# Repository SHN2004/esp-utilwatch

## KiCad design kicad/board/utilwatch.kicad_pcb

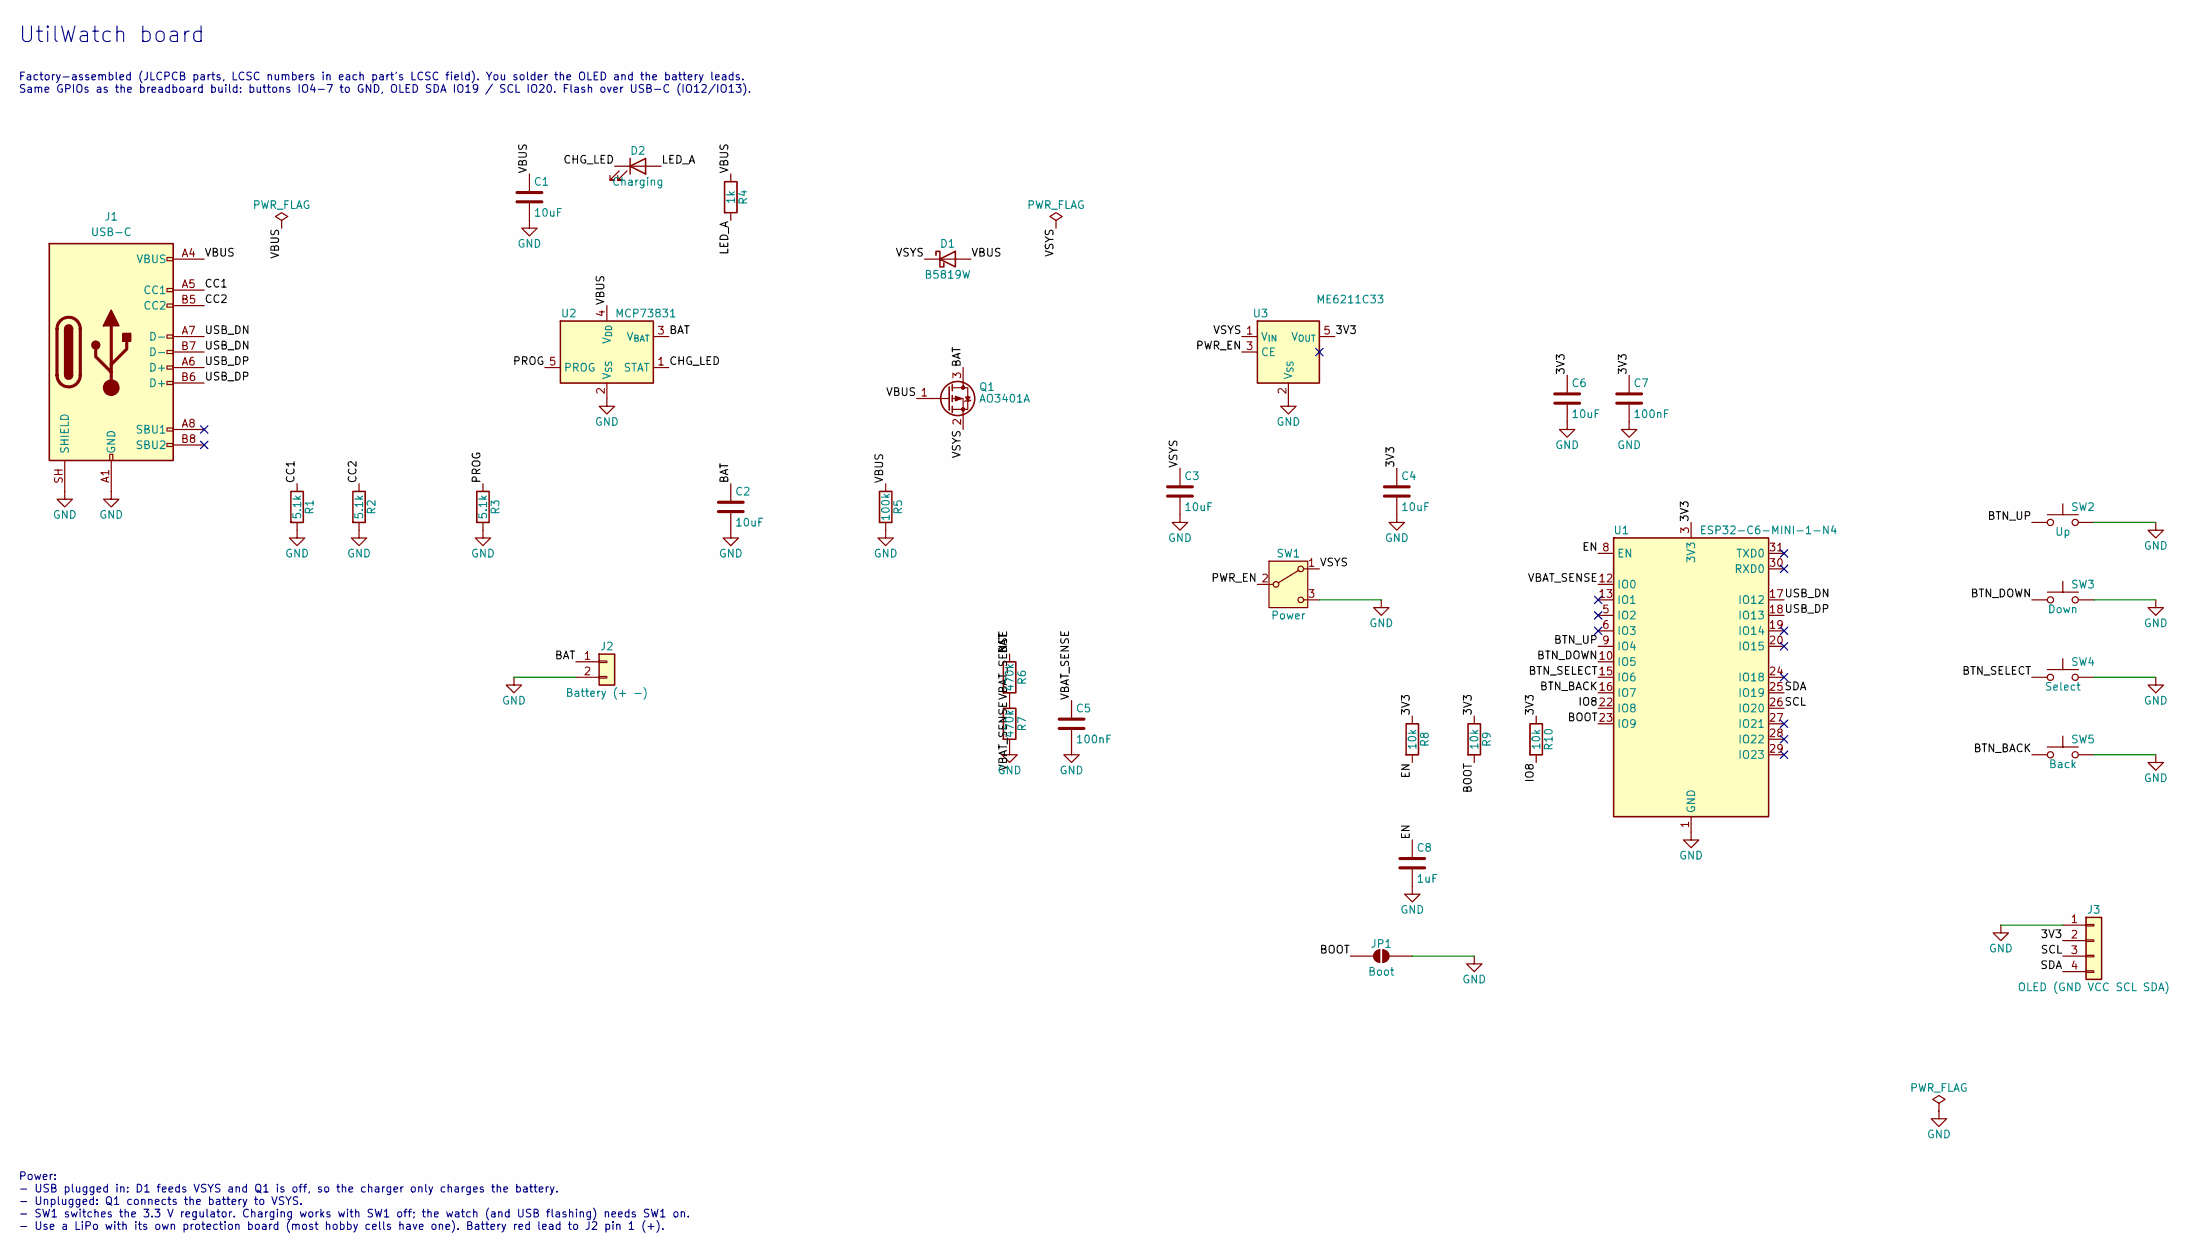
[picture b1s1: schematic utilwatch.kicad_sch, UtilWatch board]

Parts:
C1, C2, C3, C4, C6: 10uF; C_0603_1608Metric; LCSC C19702
C5, C7: 100nF; C_0603_1608Metric; LCSC C14663
C8: 1uF; C_0603_1608Metric; LCSC C15849
D1: B5819W; D_SOD-123; LCSC C8598
D2: Charging; LED_0603_1608Metric; LCSC C2286
J1: USB-C; USB_C_Receptacle_HRO_TYPE-C-31-M-12; LCSC C165948
J2: Battery (+ -); PinHeader_1x02_P2.54mm_Vertical
J3: OLED (GND VCC SCL SDA); PinHeader_1x04_P2.54mm_Vertical
JP1: Boot; SolderJumper-2_P1.3mm_Open_RoundedPad1.0x1.5mm
Q1: AO3401A; SOT-23; LCSC C15127
R1, R2, R3: 5.1k; R_0603_1608Metric; LCSC C23186
R4: 1k; R_0603_1608Metric; LCSC C21190
R5: 100k; R_0603_1608Metric; LCSC C25803
R6, R7: 470k; R_0603_1608Metric; LCSC C23178
R8, R9, R10: 10k; R_0603_1608Metric; LCSC C25804
SW1: Power; SW_SPDT_Shouhan_MSK12C02; LCSC C431540
SW2: Up; Panasonic_EVQPUJ_EVQPUA; LCSC C128539
SW3: Down; Panasonic_EVQPUJ_EVQPUA; LCSC C128539
SW4: Select; Panasonic_EVQPUJ_EVQPUA; LCSC C128539
SW5: Back; Panasonic_EVQPUJ_EVQPUA; LCSC C128539
U1: ESP32-C6-MINI-1-N4; ESP32-C6-MINI-1; LCSC C5736265
U2: MCP73831; SOT-23-5; LCSC C424093
U3: ME6211C33; SOT-23-5; LCSC C82942

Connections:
3V3: C4.1, C6.1, C7.1, J3.2, R8.1, R9.1, R10.1, U1.3 (3V3), U3.5 (V_{OUT})
BAT: C2.1, J2.1, Q1.3 (D), R6.1, U2.3 (V_{BAT})
BOOT: JP1.1 (A), R9.2, U1.23 (IO9)
BTN_BACK: SW5.1, U1.16 (IO7)
BTN_DOWN: SW3.1, U1.10 (IO5)
BTN_SELECT: SW4.1, U1.15 (IO6)
BTN_UP: SW2.1, U1.9 (IO4)
CC1: J1.A5 (CC1), R1.1
CC2: J1.B5 (CC2), R2.1
CHG_LED: D2.1 (K), U2.1 (STAT)
EN: C8.1, R8.2, U1.8 (EN)
GND: C1.2, C2.2, C3.2, C4.2, C5.2, C6.2, C7.2, C8.2, J1.A1 (GND), J1.A12 (GND), J1.B1 (GND), J1.B12 (GND), J1.SH (SHIELD), J2.2, J3.1, JP1.2 (B), R1.2, R2.2, R3.2, R5.2, R7.2, SW1.3 (C), SW2.2, SW3.2, SW4.2, SW5.2, U1.1 (GND), U1.2 (GND), U1.11 (GND), U1.14 (GND), U1.36 (GND), U1.37 (GND), U1.38 (GND), U1.39 (GND), U1.40 (GND), U1.41 (GND), U1.42 (GND), U1.43 (GND), U1.44 (GND), U1.45 (GND), U1.46 (GND), U1.47 (GND), U1.48 (GND), U1.49 (GND), U1.50 (GND), U1.51 (GND), U1.52 (GND), U1.53 (GND), U2.2 (V_{SS}), U3.2 (V_{SS})
IO8: R10.2, U1.22 (IO8)
LED_A: D2.2 (A), R4.2
PROG: R3.1, U2.5 (PROG)
PWR_EN: SW1.2 (B), U3.3 (CE)
SCL: J3.3, U1.26 (IO20)
SDA: J3.4, U1.25 (IO19)
USB_DN: J1.A7 (D-), J1.B7 (D-), U1.17 (IO12)
USB_DP: J1.A6 (D+), J1.B6 (D+), U1.18 (IO13)
VBAT_SENSE: C5.1, R6.2, R7.1, U1.12 (IO0)
VBUS: C1.1, D1.2 (A), J1.A4 (VBUS), J1.A9 (VBUS), J1.B4 (VBUS), J1.B9 (VBUS), Q1.1 (G), R4.1, R5.1, U2.4 (V_{DD})
VSYS: C3.1, D1.1 (K), Q1.2 (S), SW1.1 (A), U3.1 (V_{IN})

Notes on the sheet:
UtilWatch board
Factory-assembled (JLCPCB parts, LCSC numbers in each part's LCSC field). You solder the OLED and the battery leads. Same GPIOs as the breadboard build: buttons IO4-7 to GND, OLED SDA IO19 / SCL IO20. Flash over USB-C (IO12/IO13).
Power: - USB plugged in: D1 feeds VSYS and Q1 is off, so the charger only charges the battery. - Unplugged: Q1 connects the battery to VSYS. - SW1 switches the 3.3 V regulator. Charging works with SW1 off; the watch (and USB flashing) needs SW1 on. - Use a LiPo with its own protection board (most h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

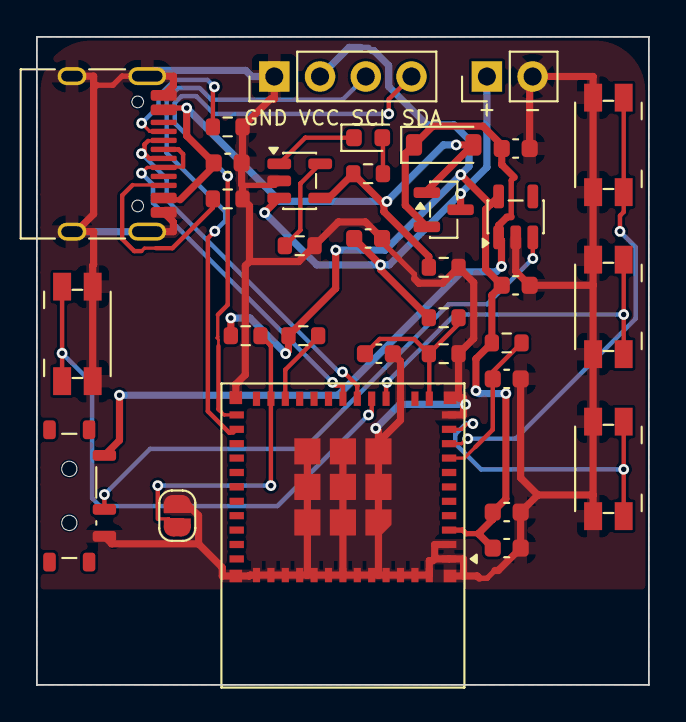
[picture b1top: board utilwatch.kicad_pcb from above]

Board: 2 copper layers, 34.0 x 36.0 mm, 33 parts (0 on the bottom side), 23 nets.

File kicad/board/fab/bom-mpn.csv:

Qty,Designator,Value,Description,Manufacturer,MPN,Package,LCSC Part #
5,"C1,C2,C3,C4,C6",10uF,Cap ceramic 10uF 10V X5R 0603,Samsung Electro-Mechanics,CL10A106KP8NNNC,C_0603_1608Metric,C19702
2,"C5,C7",100nF,Cap ceramic 100nF 50V X7R 0603,YAGEO,CC0603KRX7R9BB104,C_0603_1608Metric,C14663
1,C8,1uF,Cap ceramic 1uF 50V X5R 0603,Samsung Electro-Mechanics,CL10A105KB8NNNC,C_0603_1608Metric,C15849
1,D1,B5819W,Schottky diode 40V 1A SOD-123,JSCJ,B5819W SL,D_SOD-123,C8598
1,D2,Charging,LED red 0603,Hubei KENTO,KT-0603R,LED_0603_1608Metric,C2286
1,J1,USB-C,USB-C receptacle 16-pin SMD,Korean Hroparts (HRO),TYPE-C-31-M-12,USB_C_Receptacle_HRO_TYPE-C-31-M-12,C165948
1,Q1,AO3401A,P-MOSFET 30V 4A SOT-23,Alpha & Omega (AOS),AO3401A,SOT-23,C15127
3,"R1,R2,R3",5.1k,Resistor 5.1k 1% 0603,UNI-ROYAL,0603WAF5101T5E,R_0603_1608Metric,C23186
1,R4,1k,Resistor 1k 1% 0603,UNI-ROYAL,0603WAF1001T5E,R_0603_1608Metric,C21190
1,R5,100k,Resistor 100k 1% 0603,UNI-ROYAL,0603WAF1003T5E,R_0603_1608Metric,C25803
2,"R6,R7",470k,Resistor 470k 1% 0603,UNI-ROYAL,0603WAF4703T5E,R_0603_1608Metric,C23178
3,"R8,R9,R10",10k,Resistor 10k 1% 0603,UNI-ROYAL,0603WAF1002T5E,R_0603_1608Metric,C25804
1,SW1,Power,"Slide switch SPDT SMD, side lever",SHOU HAN,MSK12C02,SW_SPDT_Shouhan_MSK12C02,C431540
4,"SW2,SW3,SW4,SW5",Up/Down/Select/Back,Tactile switch SMD right-angle 2.2N,Panasonic,EVQ-PUA02K,Panasonic_EVQPUJ_EVQPUA,C128539
1,U1,ESP32-C6-MINI-1-N4,"Wi-Fi 6/BLE 5 module, 4MB flash",Espressif,ESP32-C6-MINI-1-N4,ESP32-C6-MINI-1,C5736265
1,U2,MCP73831,Li-ion charger SOT-23-5,Microchip,MCP73831T-2ACI/OT,SOT-23-5,C424093
1,U3,ME6211C33,LDO 3.3V 500mA SOT-23-5,MICRONE,ME6211C33M5G-N,SOT-23-5,C82942

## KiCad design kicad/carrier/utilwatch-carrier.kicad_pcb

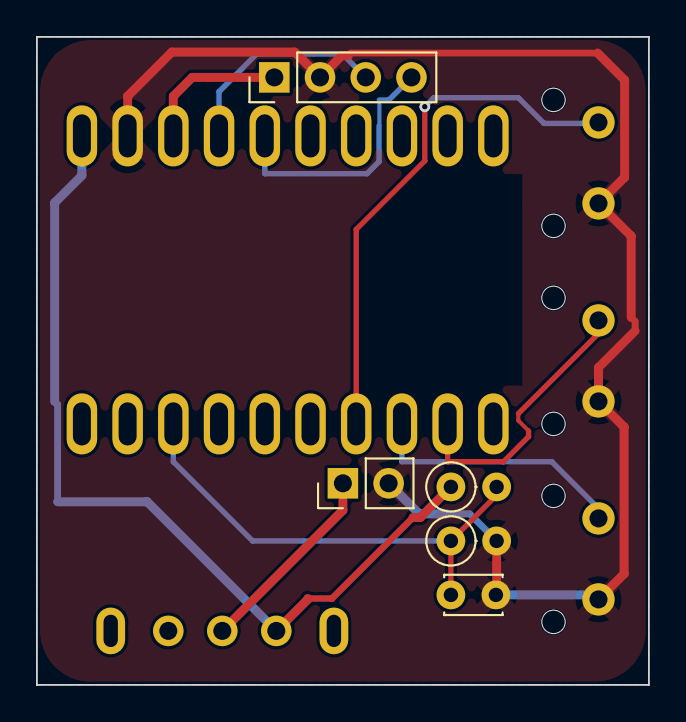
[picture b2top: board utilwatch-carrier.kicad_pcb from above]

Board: 2 copper layers, 34.0 x 36.0 mm, 10 parts (0 on the bottom side), 10 nets.

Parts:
C1: 100nF; C_Disc_D3.0mm_W2.0mm_P2.50mm
J1: OLED; PinHeader_1x04_P2.54mm_Vertical
J2: TP4056 OUT; PinHeader_1x02_P2.54mm_Vertical
R1, R2: 100k; R_Axial_DIN0207_L6.3mm_D2.5mm_P2.54mm_Vertical
SW1: Power switch; SW_Slide_SS-12F23_Angled
SW2: Up; SW_Tactile_6mm_Angled_Bracket
SW3: Down; SW_Tactile_6mm_Angled_Bracket
SW4: Select; SW_Tactile_6mm_Angled_Bracket
U1: ESP32-C6 SuperMini; ESP32-C6_SuperMini_Slotted

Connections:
3V3: J1.1, U1.13
BTN_DOWN: SW3.1, U1.8
BTN_SELECT: SW4.1, U1.9
BTN_UP: SW2.1, U1.7
GND: C1.2, J1.2, J2.2, R2.2, SW2.2, SW3.2, SW4.2, U1.12
SCL: J1.3, U1.14
SDA: J1.4, U1.15
VBAT_SENSE: C1.1, R1.2, R2.1, U1.3
VOUT: J2.1, SW1.2
VSYS: R1.1, SW1.3, U1.11

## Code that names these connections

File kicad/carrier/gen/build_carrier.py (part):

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NETS = {  # (ref, pin) -> net, from kicad/perfboard (same circuit)
    ("U1", "11"): "VSYS", ("U1", "12"): "GND", ("U1", "13"): "3V3", ("U1", "14"): "SCL",
    ("U1", "15"): "SDA", ("U1", "3"): "VBAT_SENSE", ("U1", "7"): "BTN_UP", ("U1", "8"): "BTN_DOWN",
    ("U1", "9"): "BTN_SELECT",   # pin 10 (GPIO7) is free: Back is a long press of Select
    ("J1", "1"): "3V3", ("J1", "2"): "GND", ("J1", "3"): "SCL", ("J1", "4"): "SDA",   # OLED, VCC GND SCL SDA as printed on the module
    ("SW2", "1"): "BTN_UP", ("SW3", "1"): "BTN_DOWN", ("SW4", "1"): "BTN_SELECT",
    ("SW2", "2"): "GND", ("SW3", "2"): "GND", ("SW4", "2"): "GND",
    ("R1", "1"): "VSYS", ("R1", "2"): "VBAT_SENSE", ("R2", "1"): "VBAT_SENSE", ("R2", "2"): "GND",
    ("C1", "1"): "VBAT_SENSE", ("C1", "2"): "GND",
    ("SW1", "3"): "VSYS", ("SW1", "2"): "VOUT",        # pin 1 (the switch's other throw) is unused
    ("J2", "1"): "VOUT", ("J2", "2"): "GND",           # TP4056 OUT+ / OUT-
}

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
